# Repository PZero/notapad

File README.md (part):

<div align="center">

# notªpad

**An open wearable voice recorder with an open data layer. It records all day and keeps your recordings on devices you own; open, documented interfaces (files, JSON and an MCP server) let you choose which tools use them. A resin monolith you wear around your neck.**

### [▶ Live animated presentation](https://pzero.github.io/notapad/)

**Follow the build:** [Instagram](https://www.instagram.com/notapadlabs/) · [YouTube](https://www.youtube.com/@notapadlabs) · [TikTok](https://www.tiktok.com/@notapadlabs) · **Support it:** [Ko-fi](https://ko-fi.com/notapad)

</div>

## Contents
- [Overview](#overview)
- [The object](#the-object)
- [Architecture](#architecture)
- [How it works (planned)](#how-it-works-planned)
- [Electronics v0.1](#electronics-v01)
- [Pre-order verification](#pre-order-verification)
- [First firmware and app tests](#first-firmware-and-app-tests)
- [Test bench: exploration now, MCP server later](#test-bench-exploration-now-mcp-server-later)
- [Wallpapers](#wallpapers)
- [Manufacturing](#manufacturing)
- [Status and roadmap](#status-and-roadmap)
- [Support the project](#support-the-project)
- [Project history](#project-history)
- [Repository layout](#repository-layout)
- [Contributing](#contributing)
- [License](#license)
- [Authors](#authors)

## Overview
notªpad is a wearable recorder in the spirit of Plaud and Omi, but open. Two things set it apart: **continuous recording all day** and an **open MCP server**. It records all day, syncs over Bluetooth LE with a phone, and hands the audio to an **open MCP server**. The device itself only records: what happens next (playback, search, transcription, notes) is up to the tools the user picks, not a closed service.

Design goals:
- **Own your data.** Audio and notes stay with the user; every tool that reads them is replaceable.
- **No screen, no app to open.** Interaction is a squeeze gesture, three LEDs and a vibration motor.
- **Buildable by a small team.** Off-the-shelf parts (an Ebyte E73 nRF52840 module), a 4-layer board assembled by a PCBA service, a resin shell cast in a silicone mould.

> Honest status: this is a design in progress. Nothing has been manufactured yet; the first firmware and app tests (on a development board) have run on a development board (connection, recording, download and transcription work; deeper tests are pending). Figures such as runtime and capacity are estimates.

## The object
| | |
|---|---|
| Size | about 41 × 17.5 × 9 mm (it was 8 mm until 22 Nov; 38 mm is the board length), cast resin |
| Attachment | steel ring cast in with a bushing, so it cannot come off |
| Controls | touch sensors on **both** sides (metal strips as electrodes); a touch counts only when both are active (the "squeeze" gesture), to avoid accidental triggers from the chest |
| Signalling | 3 RGB LEDs behind a 10 mm front slit, vibration motor |
| Audio | 2 PDM microphones: one on the front face, one on the top face next to the ring (via a small channel) |
| Contacts | 4 exposed gold contacts on the back: 5V, GND (charging), SWDIO, SWCLK (firmware over cable in v0.1, later also OTA over BLE). They are also a deliberate aesthetic feature. Pogo pins live in the dock, not on the monolith |

| Back | Side | Finish options |
|---|---|---|
|  |  |  |

## Architecture
```mermaid
flowchart LR
  MIC[2 PDM microphones] --> NRF[nRF52840<br/>LC3 2x24 kbit/s]
  TOUCH[Touch sensors A+B] --> NRF
  NRF --> NAND[(256 MB NAND)]
  NRF --> OUT[3 RGB LEDs + vibration]
  NRF <-->|BLE| APP[Phone app]
  APP --> MCP[Open MCP server]
  MCP --> AI[Tools of the user's choice<br/>players, notes, transcription]
```
The real app and the MCP server are not started yet; a test app for a development board exists (see the roadmap).

### How it works (planned)
Next / planned, defined on 25 Nov 2026 and not built yet. It is a loop, and day to day you only use the app. The animated version is on the [presentation page](https://pzero.github.io/notapad/#how).
```mermaid
flowchart LR
  DEV[notªpad] -->|Bluetooth LE| APP[App<br/>desktop and mobile, same data]
  APP --> SRV[notªpad server<br/>backend + MCP server]
  SRV --> AI[Your tools<br/>for example an AI assistant]
  AI --> ART[Artifact<br/>interactive page]
  ART --> APP
```
1. The notªpad syncs its audio to the app; the app sends transcripts to the notªpad server.
2. The server is only a go-between (backend plus an open MCP server). Raw transcripts go to the user's own AI and are then deleted from the server; the data stays the user's. The server could also be self-hosted.
3. The AI of the user's choice runs a preset agent template: it splits the day into segments, summarises, links and shows.
4. The result is an interactive artifact, shown back in the app.

**Voice commands and integrations.** Working today in the test app: a spoken "Command, turn on the kitchen light" turns on a light (the test app calls Home Assistant directly). Next / planned: through MCP, the user's AI could act on other tools (calendar, tasks, notes, files, any MCP server).

## Electronics v0.1
- **Module:** Ebyte E73-2G4M08S1C (nRF52840), wire antenna at the board edge with keep-out.
- **Storage:** W25N02KV QSPI NAND, 256 MB (about 10 to 11 h of stereo LC3 audio).
- **Microphones:** the front one is an MSM261DGT006 (top-port PDM). On 25 Nov it replaced the MSM261DGT003 with the updated version indicated by its manufacturer; footprint and pinout still to be confirmed against the datasheet. Since 24 Nov the top one is a Vesper VM3011, a PDM microphone with acoustic wake-up: it listens with the clock stopped at about 10 uA (datasheet figure, preliminary) and wakes the processor when sound passes a self-adapting threshold. Stereo on a single data line.
- **Motion and sound emitter (24 Nov):** a 3-axis accelerometer (LIS2DH12, I2C) and a 4 x 4 mm magnetic buzzer on the back, driven by the second half of a dual MOSFET shared with the vibration motor. The joint Apple/Google specification against unwanted tracking (DULT) asks for a sound emitter (at least 60 phon at 25 cm) and recommends a motion sensor. **This is hardware preparation only, not compatibility:** Google requires registration and certification, and Apple requires its MFi programme, whose specifications are not public.
- **Power:** ~110 mAh LiPo (381620 candidate) with protection circuit, MCP73832 charger at 50 mA, 3.3 V LDO, and a P-MOSFET latch that disconnects everything when the battery reaches 3.50 V (idle draw below ~5 uA). The 5V contact re-arms the latch, goes directly to the nRF52840 VBUS pin (internal detection; the charger status read was dropped to free pins) and resets the MCU ("reset by putting it on charge"). A watchdog is always on.
- **Board:** 16.5 x 38 mm, 4 layers, 1.0 mm, ENIG or lead-free HASL (to be fixed at order), components on the top side only. Stackup: F.Cu signals, In1 continuous GND, In2 signals and power, B.Cu signals and GND; antenna keep-out on all layers. Zones: A (0-7 mm: pins, top microphone, charger, latch), B (7-20 mm: LEDs, touch ICs, LDO, passives), C (20-38 mm: E73 module and antenna). The motor and battery sit under the board.
- **Battery:** the 502025, 602030, 401020, 401230 and 402020 cells were ruled out (too wide, too long or too small). The candidate is the 381620 (3.8 x 16 x 20 mm, about 110 mAh, estimate from listings), with protection still to be confirmed; the 501520 does not fit the 9 mm monolith.
- **Estimated consumption:** about 4.6 mA average while recording, so about 20 h on the 110 mAh cell (estimate from datasheets, little margin without the DC-DC converter; to be measured). Memory, not battery, sets the limit for continuous recording: about 11 to 12 h of stereo audio in 256 MB, stretched by recording only when there is sound and by syncing during the day.

### What changed during design review (21 Nov 2026)
- **Pinout redone.** The E73 does not expose P0.11, P0.14, P0.16, P0.19, P0.21, P0.23, P0.25, P0.27 and P1.01, which the first pinout used. The new assignment is in [`docs/pinout_v0.1.md`](docs/pinout_v0.1.md); the 32 kHz crystal is dropped (firmware uses the internal LFRC).
- **Microphones replaced.** The first choice (LMD3526B261) is bottom-port; the MSM261DGT003 is top-port and in stock (replaced on 25 Nov by the updated MSM261DGT006, see the update below).
- **Space savings.** One resistor per LED on the common anode instead of one per colour (LEDs multiplexed, one colour at a time); an extra 1 uF capacitor on the latch so a reset at low battery does not power the device off.
- **Board closed on 4 layers.** With 2 layers 7 connections stayed open; the economy assembly tier does not accept 4 layers at 0.8 mm, so the board is 1.0 mm. Length fixed at 38 mm (at 35 mm 4 connections stayed open). Checks: ERC 0, DRC 0 violations, 0 unconnected, schematic-board parity 0.
- **Charger changed to MCP73831** (50 mA), chosen at the time to keep the number of extra-fee components down. *Superseded on 22 Nov by the MCP73832, see the pre-order verification below.*
- **Manufacturing route first fixed (late 21 Nov).** The XIAO carrier variant costs more than the E73 module, is 17.5 mm wide (as wide as the monolith) and has 13 GPIOs against about 20 needed; home assembly dropped (no hot plate or paste), so a PCBA service assembles every board. No distributor beats the one we use for the key chips, and a Basic-parts-only board is impossible (no BLE, NAND, PDM microphones, RGB LEDs or touch ICs in that library); 7 extra-fee parts stay. Q2 stays a dual 2N7002DW; NAND and charger stay extra-fee parts.
- **Parts review.** E73 variant with only an external-antenna socket rejected; the 256 MB NAND confirmed after comparing alternatives; microphones rotated by 180 degrees in the placement file (checked in the assembler's preview). An alternative manufacturing variant was prepared and dropped for v0 (no microphone stock, higher quote).
- **Charger stays on the monolith** (not in the dock): unpowered contacts outside the dock, CHRG signal available, full 4.2 V charge.

### Update, 25 Nov 2026
- **Software architecture defined** (server, MCP server, preset agent template, desktop and mobile app): see [How it works (planned)](#how-it-works-planned). A plan, not built.
- **Front microphone:** MK1 changes from the MSM261DGT003 to the MSM261DGT006, the updated version indicated by its manufacturer, who confirmed the same footprint, pinout and sound hole (the board does not change) and recommends a 0.8 to 1.0 mm hole in the resin plus a gasket. The bill of materials and KiCad files are not updated to the DGT006 yet.
- **Project identity:** public contact notapad.team@gmail.com, the name @notapadlabs on Instagram, YouTube and TikTok, NªP monogram as logo. First post ("Meet notªpad") published; posts 3 to 7 scheduled until 5 Dec (4 to 5 a week at launch, then 2). Nordic Semiconductor registered the project with its technical support.
- **One fundraising goal:** 3 to 5 prototypes (about €300), individuals and companies adding up; see [Support the project](#support-the-project).
- **Board still unfrozen.** The v0.1 board of 24 Nov stays unfrozen. The VM3011 microphone may no longer be obtainable, so an alternative wake-on-sound microphone will be evaluated.
- **Subtitle:** "an open wearable voice recorder with an open data layer": the device records, the AI is one of the tools you choose.
- **Samples and contests:** sample and development-kit requests sent to the makers of the main components (nothing received yet); the project will enter two hardware design contests (deadlines 24 and 31 Jan 2027). A European grant was considered and dropped because its rules exclude AI-assisted development.
- **Support:** donations are open on [Ko-fi](https://ko-fi.com/notapad) and through the repository's Sponsor button; GitHub Sponsors is awaiting approval.
- **Sponsor search ongoing; nothing agreed,** and no production exclusivity for now.

### Update, 24 Nov 2026
- **Board regenerated, not frozen:** same 16.5 x 38 mm, 4 layers; now with the wake-on-sound microphone, the accelerometer and the buzzer described above (ERC 0, DRC 0, parity 0, 130 vias). Still under review: buzzer volume and sound outlet, the acoustic channel of the VM3011 through the shells, and VM3011 availability (out of stock at one distributor, preliminary datasheet). The final Gerber, bill of materials and placement files come after the review.
- **Pins freed without losing functions:** 5V straight to VBUS, charger status read removed, I2C on two freed pins. Three RGB LEDs and gestures unchanged.
- **Verification rerun on the new board:** 71 tests, 45 passed, 23 known warnings, 2 not verifiable, 1 to reconfirm (a component page to read again). It found and got fixed two real errors (placement rotation of the new microphone, a footprint without courtyard); a wrong charger code in the bill of materials for the manufacturers was corrected.
- **Sponsorship:** sponsor search ongoing; nothing agreed. The manufacturer is not decided.
- **Figures corrected:** about 20 h on the 110 mAh cell (estimate); the 256 MB memory holds 11 to 12 h of continuous stereo.
- **Test bench:** firmware 0.2.0 (records only on sound) and app 0.10.0 (full-precision Whisper on the device) published; next are the Android app and the architecture of the open MCP server.
- **Non-commercial for now;** licences confirmed.

### Update, 22 Nov 2026
- **Test bench defined (evening), now one animated scene on the presentation page ([#bench](https://pzero.github.io/notapad/#bench)):** Whisper with word timing and speech detection, speaker recognition (WeSpeaker), tap gestures and first voice-command tests; see [Test bench](#test-bench-exploration-now-mcp-server-later). Exploration only; the features are meant to move into the MCP server later.
- **Licences chosen:** CERN-OHL-S-2.0 for hardware, MIT for software and documents.
- **Presentation animation fixed:** the flicker while the monolith rotates came from the internal battery model sharing a face with the shell (now 15 x 19 x 3.2 mm, 0.2 mm inside). Page layout reworked for phones; group, gesture and MCP scenes redone. Checked at 375, 390 and 1280 px, not on a real iPhone. The monolith length is 41 mm; 38 mm is the board length.
- **Wallpapers approved:** all eight phone wallpapers, published below; the three LEDs are drawn as separate lights.
- **Firmware and app tested on a development board** (see below): connection, recording and download confirmed on a real XIAO nRF52840 Sense; automatic Whisper transcription added to the app; the app stays a PWA also for Android (https page still to publish). Battery 501520 dropped (does not fit 9 mm).
- **Sponsor search started** (see below). Batteries 602030, 401020, 401230 and 402020 ruled out; 381620 is the candidate (estimates).
- **Contacts:** flat-head target contacts (monolith) and single pogo pins (charging base) identified; wiring plan for the base (8 solder joints).
- **Pre-order verification, third run:** 41 passed, 25 warnings, 1 failure, 2 not verifiable (69 tests). Charger changed to the MCP73832; monolith now **9 mm** (at 8 mm only 0.1 mm of resin was left per face, now 0.6 mm); contact targets 2.0 x 4.0 mm with the tip 0.1 mm out of the back, and the four holes widened from 1.0 to 1.1 mm (only the drill files changed, copper identical, DRC clean). The section drawing of the target in the 9 mm monolith is [`verifica/target_sezione.png`](verifica/target_sezione.png) (labels in Italian).

Documents: pinout in [`docs/pinout_v0.1.md`](docs/pinout_v0.1.md); bill of materials and netlist in [`jlc/`](jlc/); KiCad project and generators in [`kicad/`](kicad/).

## Pre-order verification
The board is generated by scripts, which makes mistakes repeatable too. On 22 Nov 2026, before paying for assembly, a reviewer agent went through the whole board with **69 automated tests in 8 areas**:

| Area | What is checked |
|---|---|
| A | Rules, ERC and DRC, also with the ignored rules switched back on |
| B | Pinout of every component against its datasheet |
| C | Schematic symbol against footprint |
| D | Circuit analysis with numbers: latch, reset, dividers, LEDs, LDO, microphones, consumption |
| E | Bill of materials and placement file for the assembler: codes, extra-fee parts, rotations |
| F | Mechanics: courtyards, stack-up in the thickness, battery, motor, LEDs in the slit, microphone ports, contacts, antenna keep-out |
| G | Gerber files |
| H | Consistency between documents |

Every value is cross-checked against at least two independent sources (datasheet, the single Python definition, schematic, netlist, board, Gerber, BOM and placement file, documents). Each test is a repeatable script in [`verifica/`](verifica/) that ends in PASS, WARN, FAIL or NOT VERIFIABLE, so the review can be rerun before every order.

**First run:** 37 passed, 26 warnings, 3 failures, 2 not verifiable. **Second run, after the charger fix:** 39 / 26 / 2 / 2. **Third run, after the 9 mm and 1.1 mm hole changes:** 41 passed, 25 warnings, 1 failure, 2 not verifiable. The real problems it found:
- **Charger.** The MCP73831 status output is tri-state and powered from the 5V rail, so it would have pulled an nRF52840 pin to about 5 V, above its maximum. Fixed by switching to the MCP73832: same footprint and pinout, open-drain output, Gerber files unchanged.
- **Assembly tier (open, the one failure left).** the assembly service lists the E73 module as standard-tier assembly only, so the 97 EUR economy-tier quote has to be rechecked before paying.
- **Thickness (fixed).** With the 3 mm module and the 3.8 mm battery, 8 mm left 0.1 mm of resin per face; at 9 mm there is 0.6 mm. Only the shells change.
- **Contact holes (fixed).** The 2.0 x 4.0 mm target contacts need 1.1 mm holes instead of 1.0 mm; only the drill files changed.

**Fourth run (24 Nov), on the regenerated board:** 71 tests, 45 passed, 23 known warnings, 2 not verifiable, 1 to reconfirm. It found two real errors, both fixed: the placement rotation of the new microphone and a footprint without courtyard.

What came out clean: ERC and DRC at 0, schematic-board parity 0, empty antenna keep-out. The remaining warnings concern shells, firmware and bring-up, not the board. A review like this cannot replace testing the real boards, and it does not guarantee they will work.

## First firmware and app tests
Started on 22 Nov 2026, before the v0.1 boards arrive. They run on a **Seeed XIAO nRF52840 Sense** with a battery: a development board with the same nRF52840 chip, a PDM microphone and 2 MB of flash, used to try the whole chain early.
- **Firmware** ([`firmware/xiao-prova/`](firmware/xiao-prova/), Arduino with the Bluefruit library): records at 16 kHz, compresses with IMA ADPCM and stores the audio in a ring of 512 sectors of 4 KB, about 4 minutes. At 80% full it asks to sync and the connected app downloads by itself. Each sector is erased only after the app has received it, verified its CRC and saved it. Shutdown at 3.50 V and a watchdog are included.
- **App** ([`app/`](app/)): a web app (PWA), local-only for now (localhost, Web Bluetooth in Edge or Chrome). It stores in the browser (IndexedDB), with playback and WAV export, and no cloud. Since 22 Nov it also **transcribes automatically after each sync** with Whisper running in the browser (transformers.js in a Web Worker, WebGPU or WASM; small model on a PC, base on a phone; Italian), keeping the time of each sentence, with TXT export. The audio never leaves the device. Test: 17 s of Italian speech in 4.8 s with whisper-base on WebGPU.
- **Honest status:** the firmware was flashed on a real XIAO nRF52840 Sense and tested with the app on 22 Nov: Bluetooth connection, recording and audio download work. **Not tested in depth yet:** automatic sync at 80%, audio quality, download speed, the small Whisper model, Edge as an installed app and an Android phone. The final firmware for the v0.1 board (Zephyr is the option) is separate and still on hold; the phone app stays a PWA for now (Flutter postponed).

## Test bench: exploration now, MCP server later
This is an **exploration phase, not the product**. The XIAO nRF52840 Sense firmware plus the local app (Web Bluetooth, data kept only in the browser) are a test bench to learn which software features work and how well, before the real board exists. Most of it was added on 22 Nov 2026 and improved on 23 Nov; speed and error rates are not measured yet.
- **Whisper in the browser** (transformers.js, models that return the time of every word): the audio never leaves the device. **Updated 23 Nov (app 0.10.0):** the decoder had been running compressed to 4 bits on WebGPU, the main cause of errors in Italian; it now runs at full precision, and on a PC with WebGPU the automatic model is large-v3-turbo (a download of about 1.6 GB, once). Audio goes to the model in windows of 10 to 25 s cut at pauses, with levelled volume and a filter for invented or repeated phrases. Transcription starts on request (automatically only for quick commands); models can be loaded from a local folder to work offline. Quality is better by observation, not measured.
- **Who is speaking:** voice prints with WeSpeaker ResNet34. The transcript shows "Me" (the owner, whose profile comes from the microphone or from confirming "that's me" on a transcript) and "Speaker 1, 2, 3...". Text is always in chronological order.
- **Gestures** on the device (motion sensor): double tap starts or stops recording; single tap is a command (5 yellow flashes, the next 6 seconds become a separate piece downloaded with priority, then recording continues).
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
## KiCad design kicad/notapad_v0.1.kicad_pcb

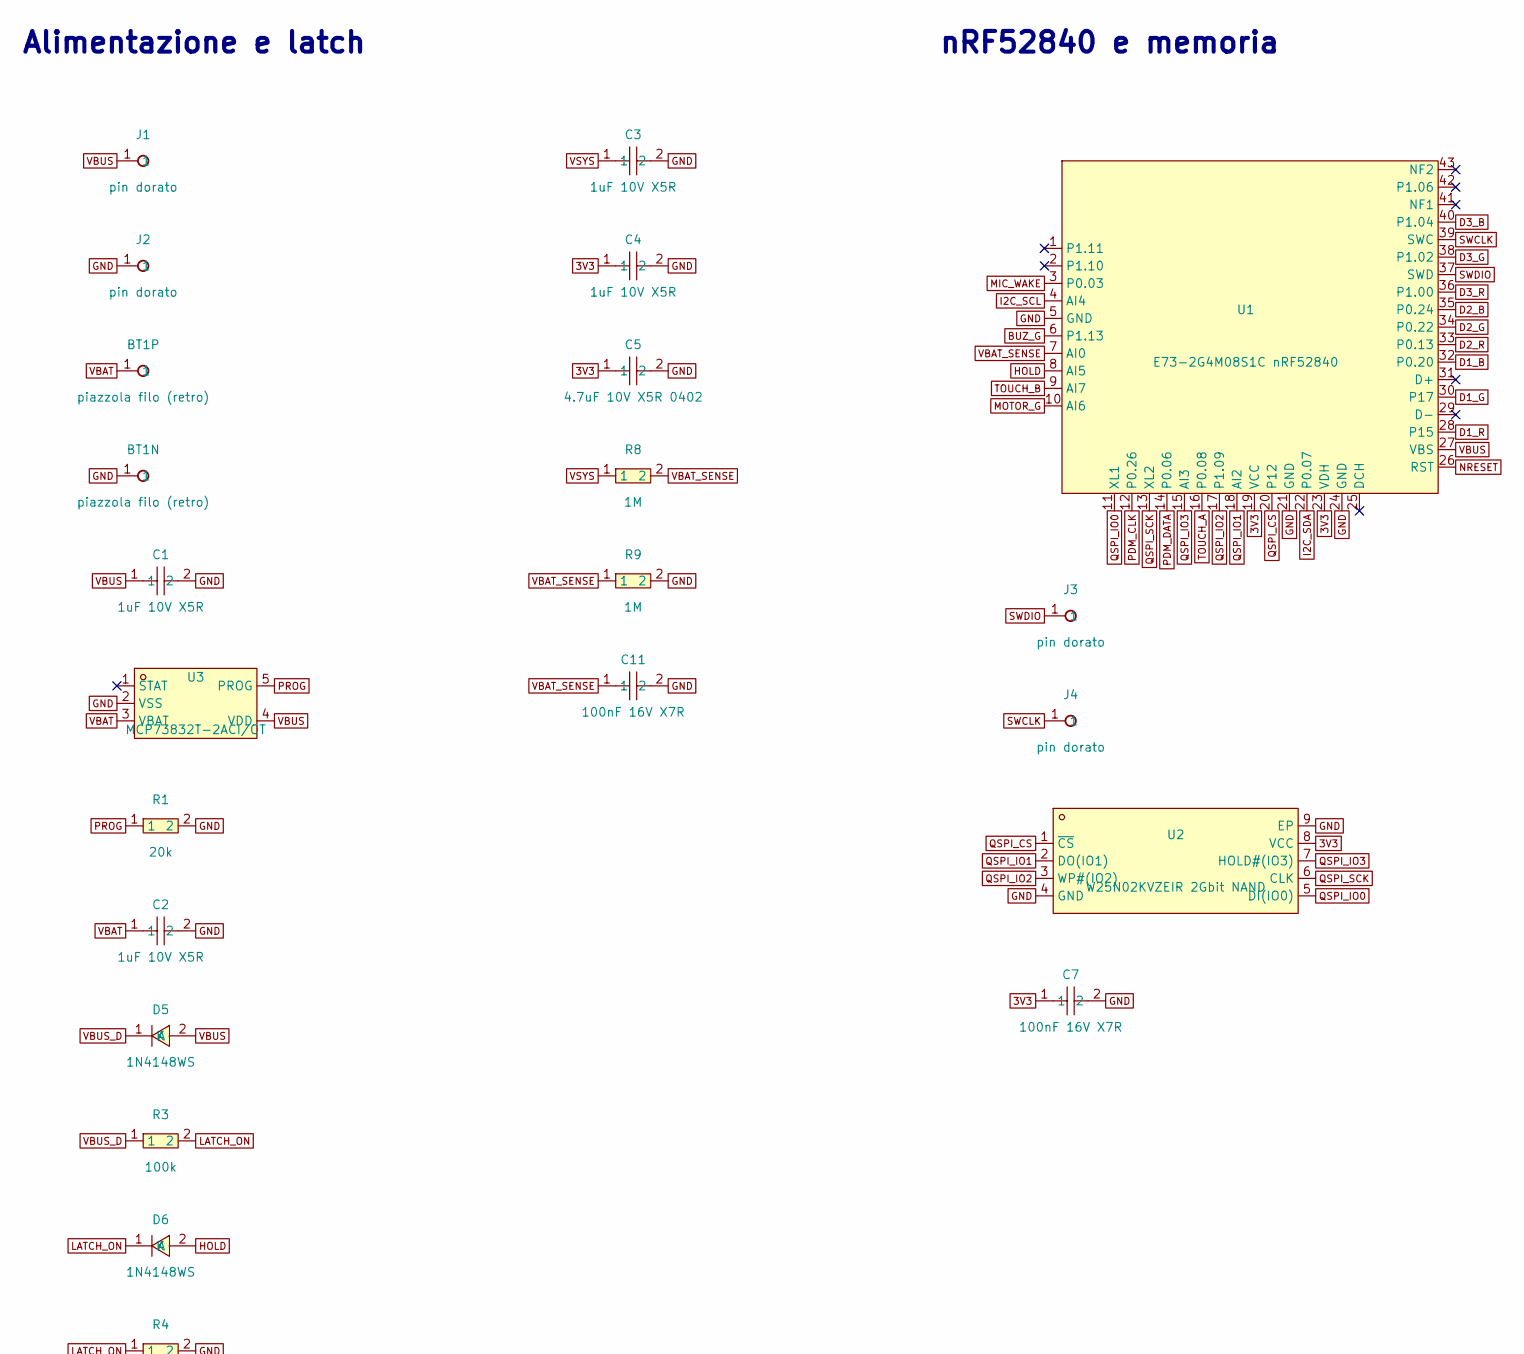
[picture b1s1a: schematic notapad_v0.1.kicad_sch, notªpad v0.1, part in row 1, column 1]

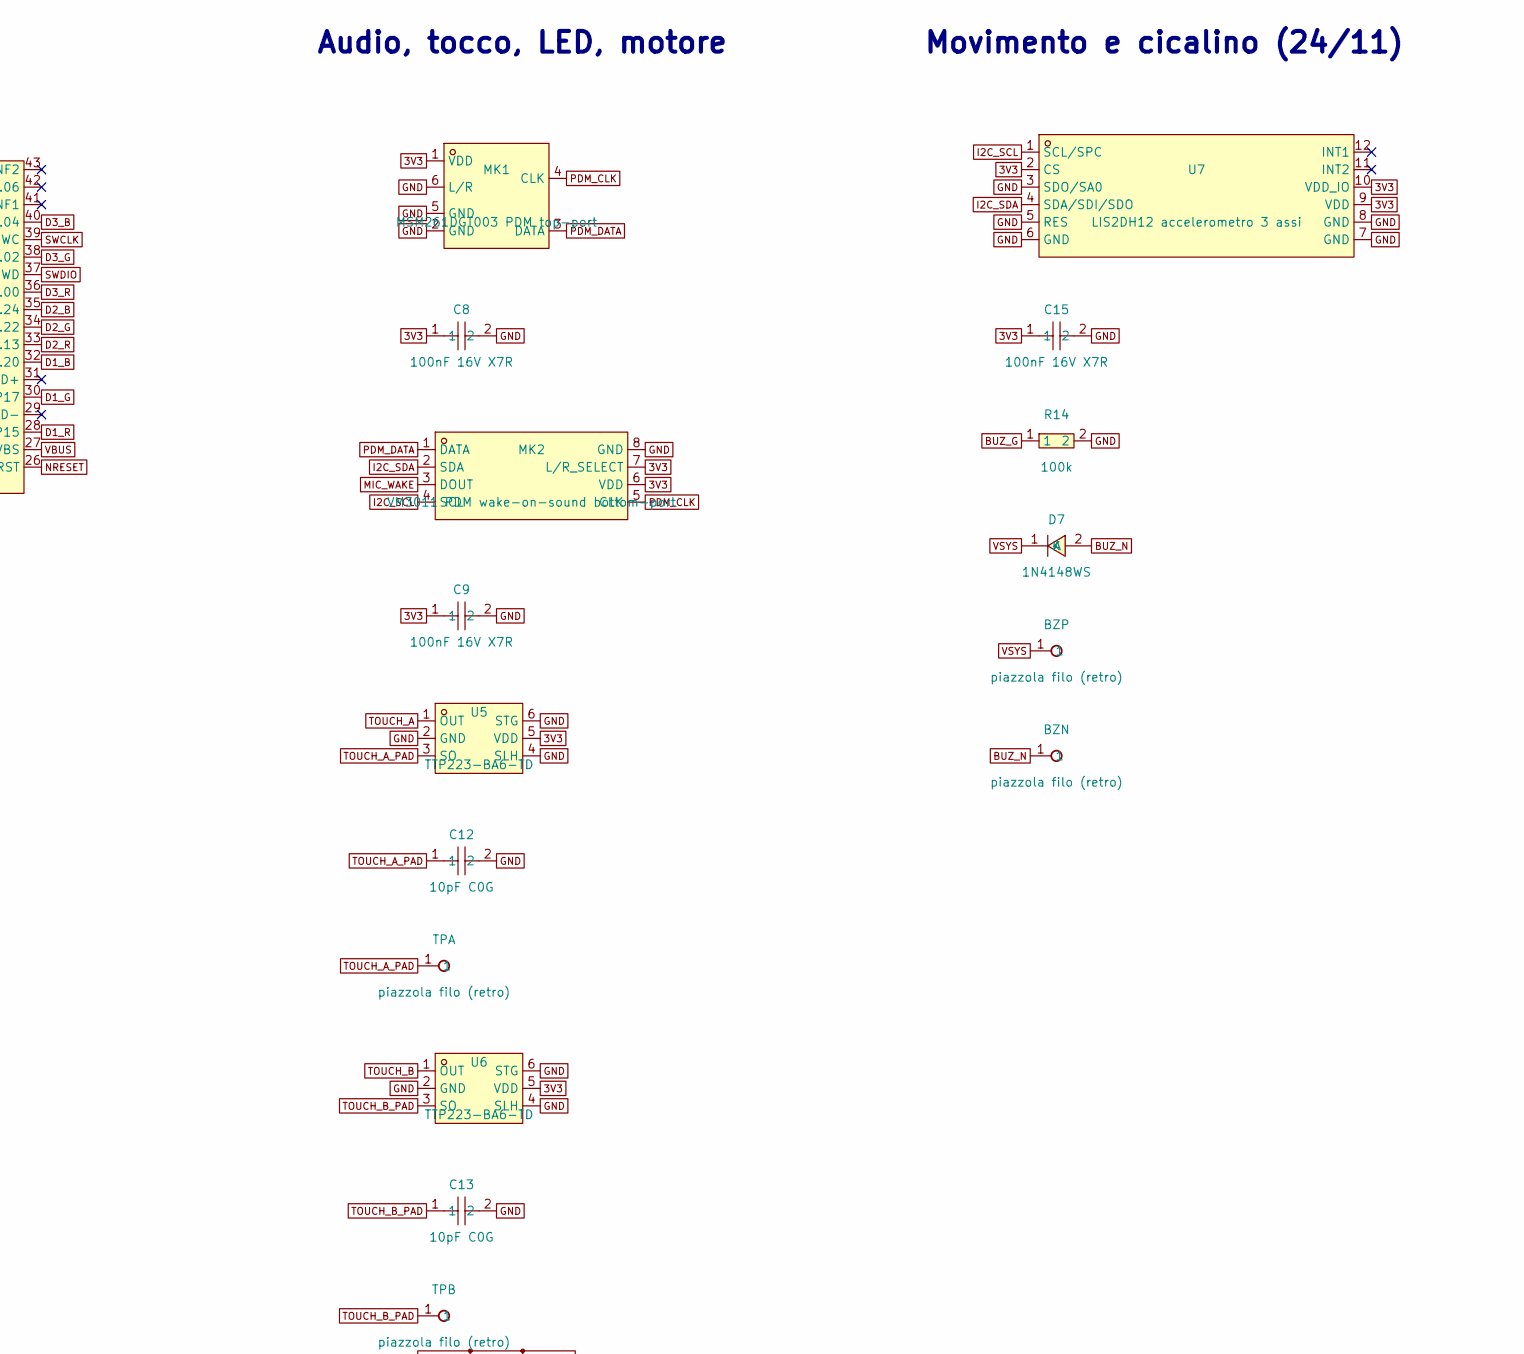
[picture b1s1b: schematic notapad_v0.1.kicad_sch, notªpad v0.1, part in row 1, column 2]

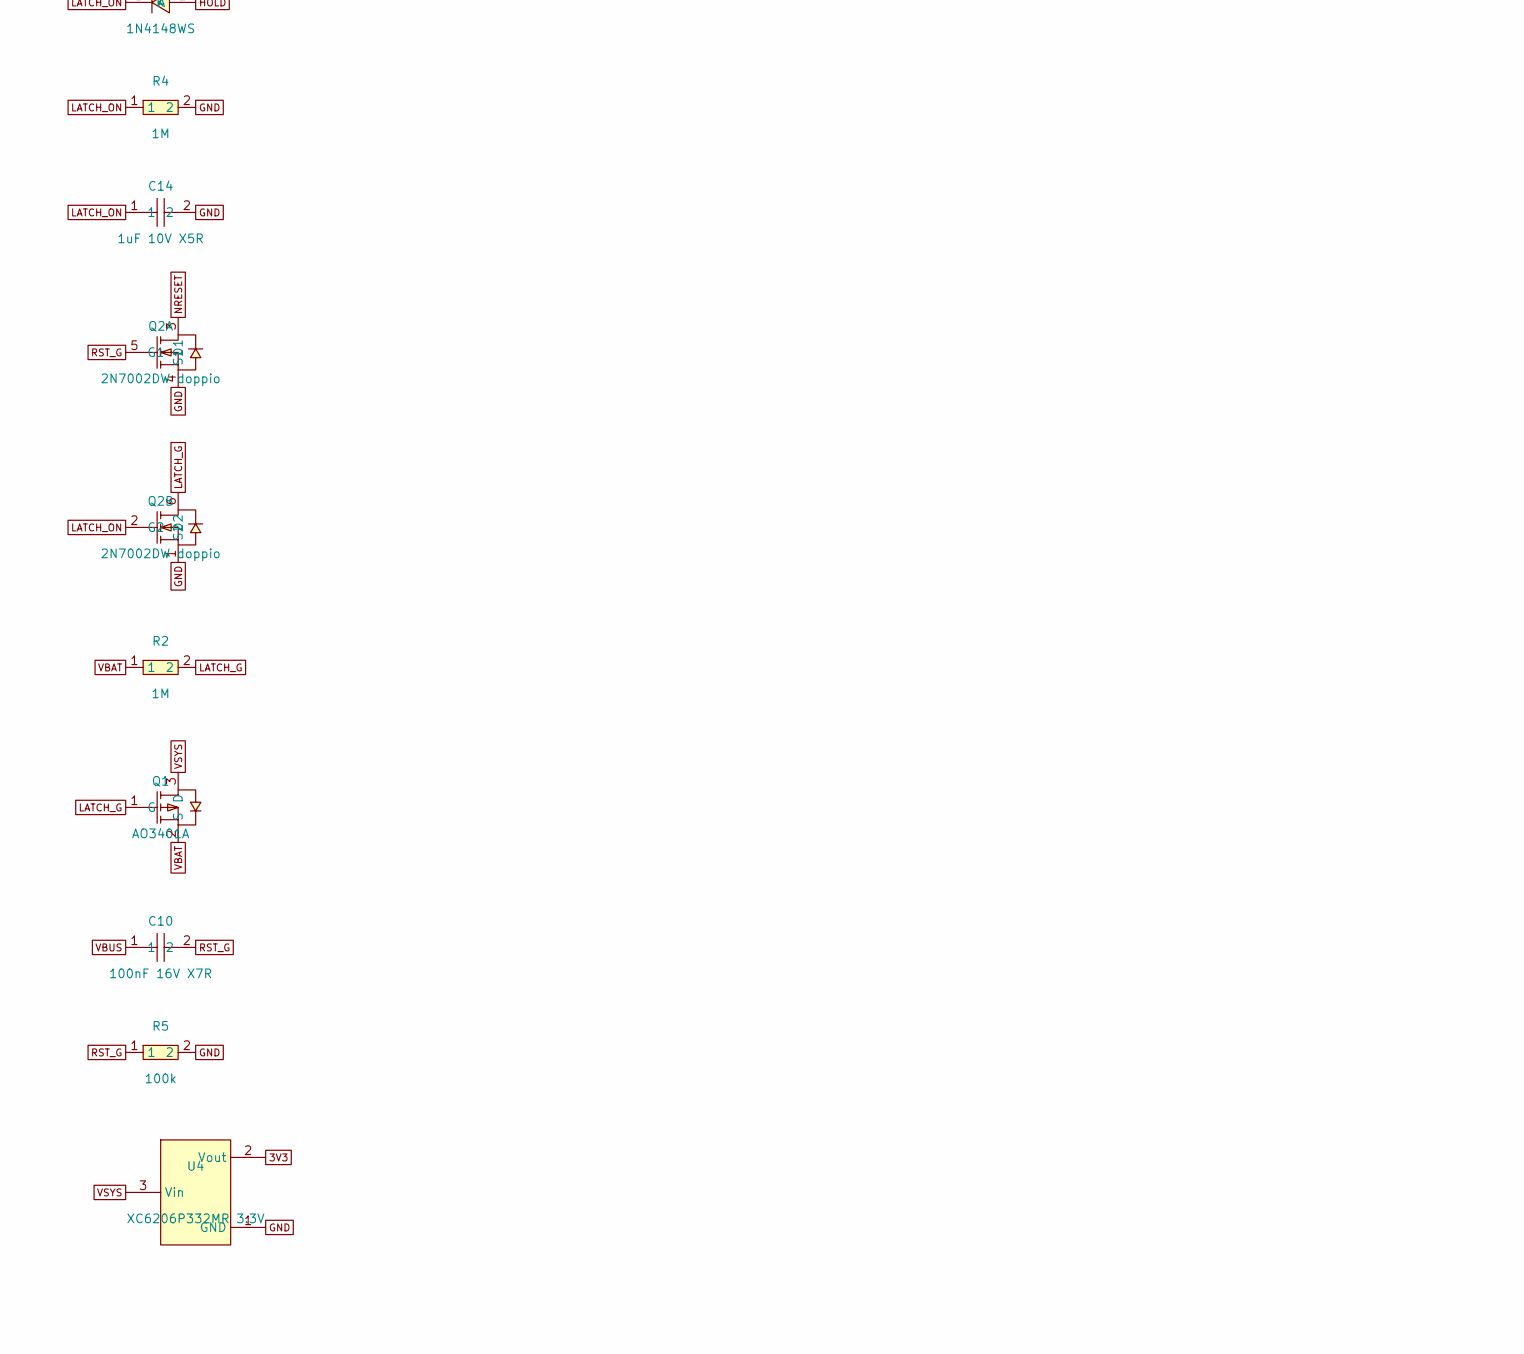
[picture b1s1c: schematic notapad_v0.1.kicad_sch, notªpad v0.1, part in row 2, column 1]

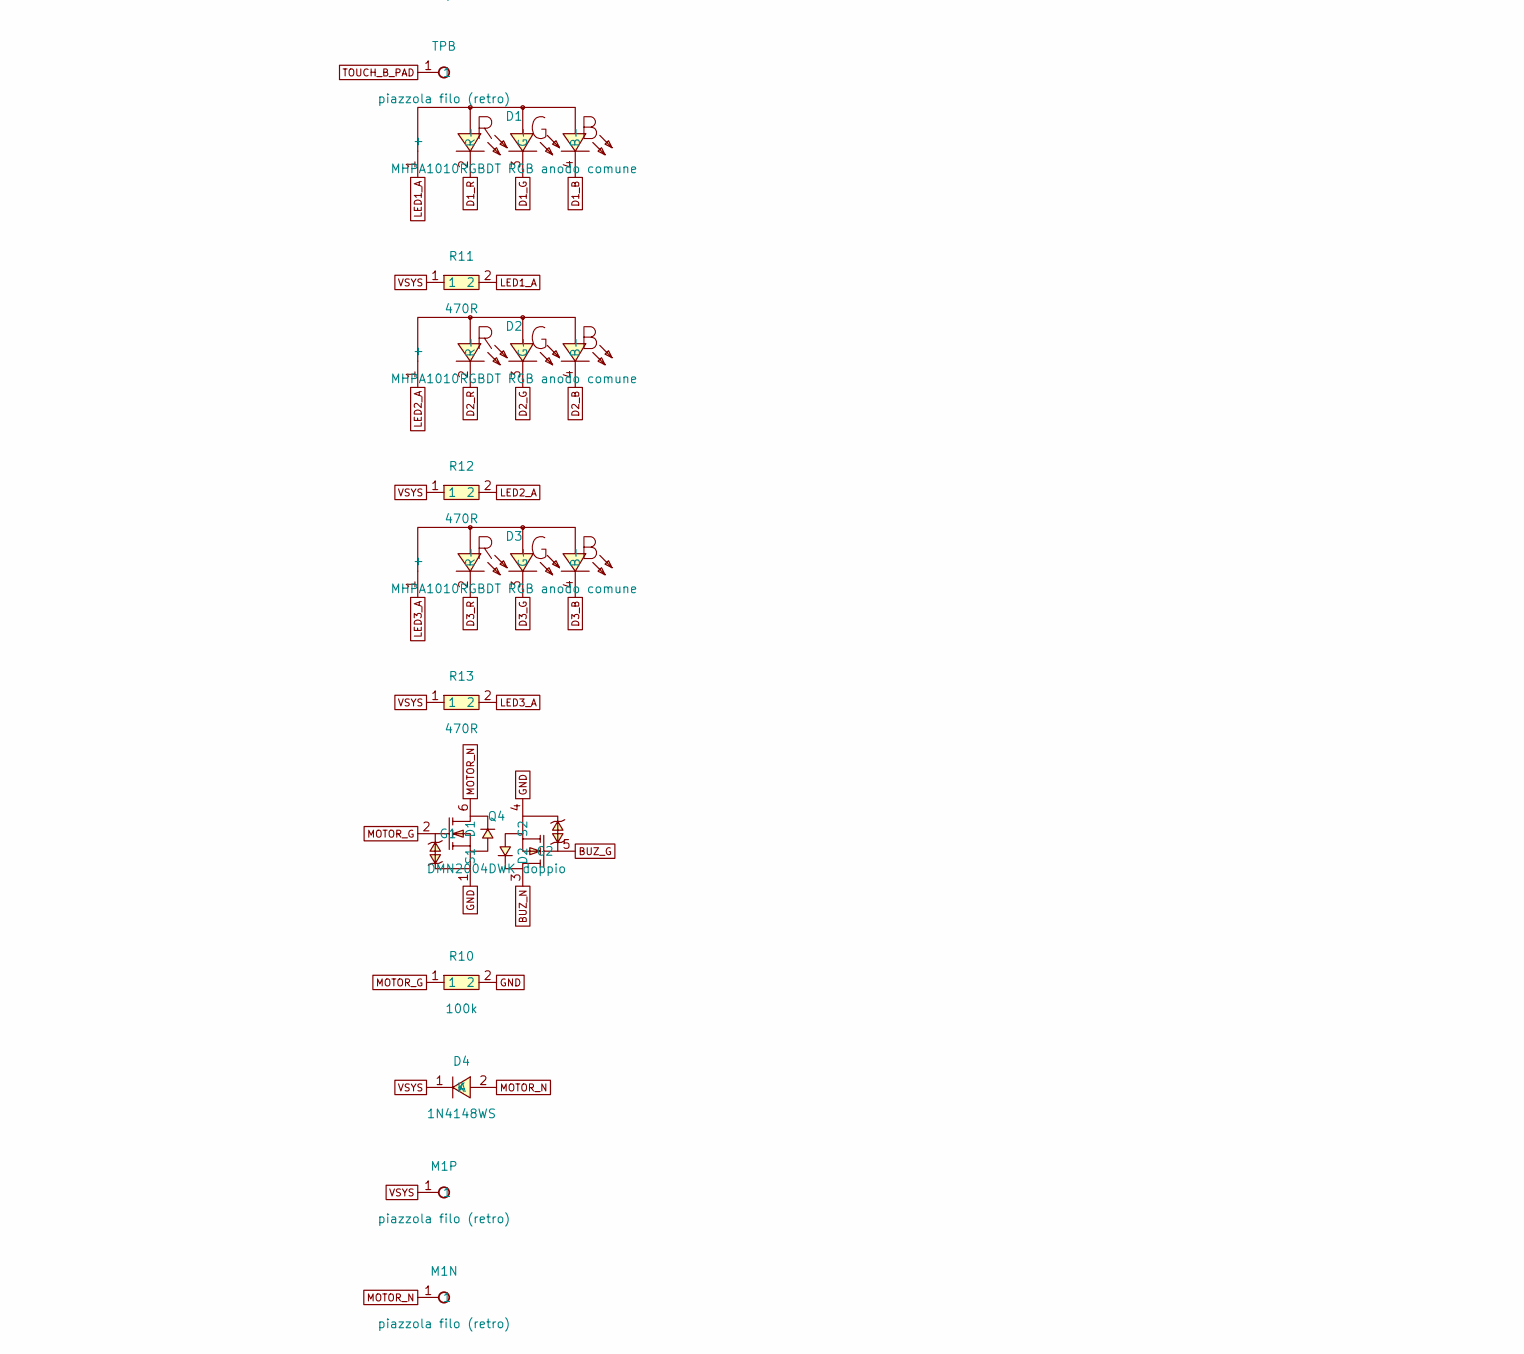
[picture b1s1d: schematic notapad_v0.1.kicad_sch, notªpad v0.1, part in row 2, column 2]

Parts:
BT1N, BT1P: piazzola filo (retro); PAD_BOT_1.2x1.6
BZN: piazzola filo (retro); PAD_BOT_1.2x1.6
BZP: piazzola filo (retro); PAD_BOT_1.2x1.6
C1, C2, C3, C4, C14: 1uF 10V X5R; C0402; LCSC Part C52923
C5: 4.7uF 10V X5R 0402; C0402; LCSC Part C23733
C7, C8, C9, C10, C11, C15: 100nF 16V X7R; C0402; LCSC Part C1525
C12, C13: 10pF C0G; C0402; LCSC Part C32949
D1, D2, D3: MHPA1010RGBDT RGB anodo comune; LED-ARRAY-SMD_4P-L1.0-W1.0-TR-RD; LCSC Part C404280
D4, D5, D6, D7: 1N4148WS; SOD-323_L1.8-W1.3-LS2.5-RD; LCSC Part C2128
J1, J2, J3, J4: pin dorato; PIN_THT_1.6
M1N, M1P: piazzola filo (retro); PAD_BOT_1.2x1.6
MK1: MSM261DGT003 PDM top-port; MIC-SMD_6P-L4.0-W2.0_LMD4020T261-OC3; LCSC Part C48227730
MK2: VM3011 PDM wake-on-sound bottom-port; SENSOR-SMD_VM3011-U1; LCSC Part C7149370
Q1: AO3401A; SOT-23_L2.9-W1.3-P1.90-LS2.4-BR; LCSC Part C15127
Q2: 2N7002DW doppio; SOT-363_L2.0-W1.3-P0.65-LS2.1-TL; LCSC Part C83571
Q4: DMN2004DWK doppio; SOT-363_L2.0-W1.3-P0.65-LS2.1-TL; LCSC Part C156343
R1: 20k; R0402; LCSC Part C25765
R2, R4, R8, R9: 1M; R0402; LCSC Part C26083
R3, R5, R10, R14: 100k; R0402; LCSC Part C25741
R11, R12, R13: 470R; R0402; LCSC Part C25117
TPA: piazzola filo (retro); PAD_BOT_1.2x1.6
TPB: piazzola filo (retro); PAD_BOT_1.2x1.6
U1: E73-2G4M08S1C nRF52840; WIRELM-SMD_E73-2G4M08S1C; LCSC Part C356849
U2: W25N02KVZEIR 2Gbit NAND; WSON-8_L8.0-W6.0-P1.27-TL-EP-1; LCSC Part C3010298
U3: MCP73832T-2ACI/OT; SOT-23-5_L3.0-W1.7-P0.95-LS2.8-BL; LCSC Part C38066
U4: XC6206P332MR 3.3V; SOT-23-3_L2.9-W1.6-P1.90-LS2.8-BR; LCSC Part C5446
U5, U6: TTP223-BA6-TD; SOT-23-6_L2.9-W1.6-P0.95-LS2.9-BL; LCSC Part C42422127
U7: LIS2DH12 accelerometro 3 assi; LGA-12_L2.0-W2.0-P0.50-BL; LCSC Part C110926

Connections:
3V3: C4.1, C5.1, C7.1, C8.1, C9.1, C15.1, MK1.1 (VDD), MK2.6 (VDD), MK2.7 (L/R_SELECT), U1.19 (VCC), U1.23 (VDH), U2.8 (VCC), U4.2 (Vout), U5.5 (VDD), U6.5 (VDD), U7.2 (CS), U7.9 (VDD), U7.10 (VDD_IO)
BUZ_G: Q4.5 (G2), R14.1, U1.6 (P1.13)
BUZ_N: BZN.1, D7.2 (A), Q4.3 (D2)
D1_B: D1.4 (B-), U1.32 (P0.20)
D1_G: D1.3 (G-), U1.30 (P17)
D1_R: D1.2 (R-), U1.28 (P15)
D2_B: D2.4 (B-), U1.35 (P0.24)
D2_G: D2.3 (G-), U1.34 (P0.22)
D2_R: D2.2 (R-), U1.33 (P0.13)
D3_B: D3.4 (B-), U1.40 (P1.04)
D3_G: D3.3 (G-), U1.38 (P1.02)
D3_R: D3.2 (R-), U1.36 (P1.00)
GND: BT1N.1, C1.2, C2.2, C3.2, C4.2, C5.2, C7.2, C8.2, C9.2, C11.2, C12.2, C13.2, C14.2, C15.2, J2.1, MK1.2 (GND), MK1.5 (GND), MK1.6 (L/R), MK2.8 (GND), Q2.1 (S2), Q2.4 (S1), Q4.1 (S1), Q4.4 (S2), R1.2, R4.2, R5.2, R9.2, R10.2, R14.2, U1.5 (GND), U1.21 (GND), U1.24 (GND), U2.4 (GND), U2.9 (EP), U3.2 (VSS), U4.1 (GND), U5.2 (GND), U5.4 (SLH), U5.6 (STG), U6.2 (GND), U6.4 (SLH), U6.6 (STG), U7.3 (SDO/SA0), U7.5 (RES), U7.6 (GND), U7.7 (GND), U7.8 (GND)
HOLD: D6.2 (A), U1.8 (AI5)
I2C_SCL: MK2.4 (SCL), U1.4 (AI4), U7.1 (SCL/SPC)
I2C_SDA: MK2.2 (SDA), U1.22 (P0.07), U7.4 (SDA/SDI/SDO)
LATCH_G: Q1.1 (G), Q2.6 (D2), R2.2
LATCH_ON: C14.1, D6.1 (K), Q2.2 (G2), R3.2, R4.1
LED1_A: D1.1 (+), R11.2
LED2_A: D2.1 (+), R12.2
LED3_A: D3.1 (+), R13.2
MIC_WAKE: MK2.3 (DOUT), U1.3 (P0.03)
MOTOR_G: Q4.2 (G1), R10.1, U1.10 (AI6)
MOTOR_N: D4.2 (A), M1N.1, Q4.6 (D1)
NRESET: Q2.3 (D1), U1.26 (RST)
PDM_CLK: MK1.4 (CLK), MK2.5 (CLK), U1.12 (P0.26)
PDM_DATA: MK1.3 (DATA), MK2.1 (DATA), U1.14 (P0.06)
PROG: R1.1, U3.5 (PROG)
QSPI_CS: U1.20 (P12), U2.1 (~CS)
QSPI_IO0: U1.11 (XL1), U2.5 (DI(IO0))
QSPI_IO1: U1.18 (AI2), U2.2 (DO(IO1))
QSPI_IO2: U1.17 (P1.09), U2.3 (WP#(IO2))
QSPI_IO3: U1.15 (AI3), U2.7 (HOLD#(IO3))
QSPI_SCK: U1.13 (XL2), U2.6 (CLK)
RST_G: C10.2, Q2.5 (G1), R5.1
SWCLK: J4.1, U1.39 (SWC)
SWDIO: J3.1, U1.37 (SWD)
TOUCH_A: U1.16 (P0.08), U5.1 (OUT)
TOUCH_A_PAD: C12.1, TPA.1, U5.3 (SO)
TOUCH_B: U1.9 (AI7), U6.1 (OUT)
TOUCH_B_PAD: C13.1, TPB.1, U6.3 (SO)
VBAT: BT1P.1, C2.1, Q1.2 (S), R2.1, U3.3 (VBAT)
VBAT_SENSE: C11.1, R8.2, R9.1, U1.7 (AI0)
VBUS: C1.1, C10.1, D5.2 (A), J1.1, U1.27 (VBS), U3.4 (VDD)
VBUS_D: D5.1 (K), R3.1
VSYS: BZP.1, C3.1, D4.1 (K), D7.1 (K), M1P.1, Q1.3 (D), R8.1, R11.1, R12.1, R13.1, U4.3 (Vin)

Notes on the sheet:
Alimentazione e latch
nRF52840 e memoria
Audio, tocco, LED, motore
Movimento e cicalino (24/11)

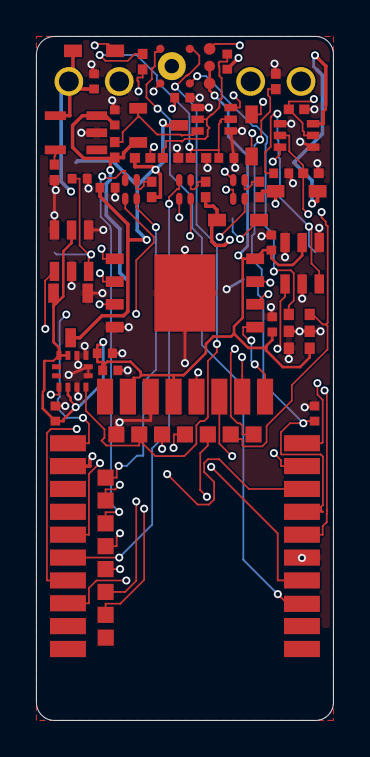
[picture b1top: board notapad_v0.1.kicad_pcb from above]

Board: 4 copper layers, 16.5 x 38.0 mm, 57 parts (0 on the bottom side), 46 nets.

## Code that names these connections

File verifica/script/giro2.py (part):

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

def B05():
    bad, p = _pinchk("U2", {"1": ("~{CS}", "QSPI_CS"), "2": ("DO(IO1)", "QSPI_IO1"), "3": ("WP#(IO2)", "QSPI_IO2"), "4": ("GND", "GND"), "5": ("DI(IO0)", "QSPI_IO0"),
                            "6": ("CLK", "QSPI_SCK"), "7": ("HOLD#(IO3)", "QSPI_IO3"), "8": ("VCC", "3V3"), "9": ("EP", "GND")})
    return ("PASS" if not bad else "FAIL"), ("1 /CS, 2 IO1, 3 IO2, 4 GND, 5 IO0, 6 CLK, 7 IO3, 8 3V3, EP GND: coincide" if not bad else f"differenze {bad}")


def B06():
    r = {}
    r["MK1"], _ = _pinchk("MK1", {"1": ("VDD", "3V3"), "2": ("GND", "GND"), "3": ("DATA", "PDM_DATA"), "4": ("CLK", "PDM_CLK"), "5": ("GND", "GND"), "6": ("L/R", "GND")})
    # 24/11: MK2 = VM3011 (datasheet U0.0.8: 1 DATA, 2 SDA, 3 DOUT, 4 SCL, 5 CLK, 6 VDD, 7 L/R, 8 GND; VDD 1,6-3,6 V)
    r["MK2"], _ = _pinchk("MK2", {"1": ("DATA", "PDM_DATA"), "2": ("SDA", "I2C_SDA"), "3": ("DOUT", "MIC_WAKE"), "4": ("SCL", "I2C_SCL"),
                                  "5": ("CLK", "PDM_CLK"), "6": ("VDD", "3V3"), "7": ("L/R_SELECT", "3V3"), "8": ("GND", "GND")})
    ok = not any(r.values())
    return ("PASS" if ok else "FAIL"), ("MK1 MSM261: 1 VDD, 2/5 GND, 3 DATA, 4 CLK, 6 L/R=GND, top-port; MK2 VM3011: 1 DATA, 2 SDA, 3 DOUT=MIC_WAKE, 4 SCL, 5 CLK, "
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

def B07():
    bad, p = _pinchk("U3", {"2": ("VSS", "GND"), "3": ("VBAT", "VBAT"), "4": ("VDD", "VBUS"), "5": ("PROG", "PROG")})
    d = D(); lcsc, v = d.P["CHG"][2], d.P["CHG"][3]
    r1 = d.P[d.C["R1"][0]][3]
    iprog = 1000 / 20 if r1 == "20k" else None
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    if lcsc == "C424093":
        return "FAIL", "U3 è ancora MCP73831 (STAT tri-state a 5 V su P0.07)"
    if lcsc == "C38066" and not stat and "1" not in d.C["U3"][1]:
        return "PASS", ("U3 MCP73832T-2ACI/OT (C38066), STAT non collegato dal 24/11 (P0.07 ora I2C_SDA): nessun percorso dal 5V a un GPIO; "
                        "lo stato di carica si ricava da VBUS e dalla tensione della batteria")
    return "FAIL", f"configurazione inattesa: {lcsc}, rete STAT {stat}"


def B09():
    bad, _ = _pinchk("U4", {"1": ("GND", "GND"), "2": ("Vout", "3V3"), "3": ("Vin", "VSYS")})
    return ("PASS" if not bad else "FAIL"), ("1 GND, 2 Vout=3V3, 3 Vin=VSYS (Torex MR: VSS/VOUT/VIN)" if not bad else f"{bad}")


def B10():
    b1, _ = _pinchk("Q1", {"1": ("G", "LATCH_G"), "2": ("S", "VBAT"), "3": ("D", "VSYS")})
    b4, _ = _pinchk("Q4", {"1": ("S1", "GND"), "2": ("G1", "MOTOR_G"), "6": ("D1", "MOTOR_N"), "4": ("S2", "GND"), "5": ("G2", "BUZ_G"), "3": ("D2", "BUZ_N")})
    ok = not b1 and not b4
    return ("PASS" if ok else "FAIL"), ("Q1 G=LATCH_G S=VBAT D=VSYS; Q4 DMN2004DWK: FET1 S=GND G=MOTOR_G D=MOTOR_N, FET2 S=GND G=BUZ_G D=BUZ_N "
                                        "(0,5 ohm a 2,5 V, 540 mA); soglie compatibili con 3,3 V" if ok else f"{b1} {b4}")


def B11():
    bad, _ = _pinchk("Q2", {"1": ("S2", "GND"), "2": ("G2", "LATCH_ON"), "6": ("D2", "LATCH_G"), "4": ("S1", "GND"), "5": ("G1", "RST_G"), "3": ("D1", "NRESET")})
    return ("PASS" if not bad else "FAIL"), ("FET {1 S,2 G,6 D}: GND/LATCH_ON/LATCH_G; FET {4 S,5 G,3 D}: GND/RST_G/NRESET; etichette 1/2 del simbolo LCSC scambiate ma FET identici" if not bad else f"{bad}")


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

def B15():
    bad, _ = _pinchk("U7", {"1": ("SCL/SPC", "I2C_SCL"), "2": ("CS", "3V3"), "3": ("SDO/SA0", "GND"), "4": ("SDA/SDI/SDO", "I2C_SDA"), "5": ("RES", "GND"),
                            "6": ("GND", "GND"), "7": ("GND", "GND"), "8": ("GND", "GND"), "9": ("VDD", "3V3"), "10": ("VDD_IO", "3V3")})
    return ("PASS" if not bad else "FAIL"), ("U7 LIS2DH12: SCL/SDA su I2C, CS a 3V3 (modo I2C), SA0 a GND (0x18, diverso dal VM3011 0x61), RES e 6-8 a GND, "
                                             "VDD e VDD_IO 3V3, INT1/INT2 liberi (campionamento a 10 s); C15 100 nF + C5 4,7 uF vicini" if not bad else f"{bad}")
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def D16():
    d = D(); e = d.C["U1"][1]
    pin = {n: k for k, n in e.items()}
    ok = (pin.get("MIC_WAKE") == "3" and pin.get("I2C_SDA") == "22" and pin.get("I2C_SCL") == "4" and pin.get("BUZ_G") == "6"
          and not any(f.startswith("R") and n in ("I2C_SDA", "I2C_SCL") for r, (f, p, _) in d.C.items() for n in p.values())
          and d.C["BZP"][1]["1"] == "VSYS" and d.C["BZN"][1]["1"] == "BUZ_N")
    return ("PASS" if ok else "FAIL"), ("MIC_WAKE su P0.03 (pad 3), I2C su P0.07/P0.28 con pull-up interni del nRF (~13 k, 100 kHz, piste corte), "
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STATO = {"A01": "rieseguo l'ERC con kicad-cli", "A02": "rieseguo il DRC con parità schema e scollegati", "A03": "DRC severo su una copia con le regole ignorate riattivate",
         "A04": "estraggo regole, via e distanze dei fori con pcbnew", "A05": "conto le isole del piano GND In1", "A06": "estraggo il zip, riesporto i Gerber e confronto il contorno con il DXF",
         "A07": "cerco via dentro i pad SMD con le forme reali", "A08": "confronto riga per riga Gerber del zip ed export fresco", "A09": "riesporto la netlist e leggo gli avvisi",
         "B07": "confronto pin MCP73832 con simbolo e reti, R PROG e pagina JLC C38066", "B08": "verifico che STAT sia open-drain e senza pull-up verso il 5V",
         "C01": "rieseguo il confronto simbolo-impronta-def-netlist-pcb", "E01": "riesporto il pos e confronto riferimenti BOM/CPL", "E02": "codici LCSC, Value e conteggio Extended con C38066",
         "E03": "rileggo la pagina JLC dell'E73", "G01": "strati presenti nel nuovo zip", "H05": "riga STAT di pinout.md contro il caricatore montato"}

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
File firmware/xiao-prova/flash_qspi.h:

// notªpad - driver minimo della flash QSPI della XIAO nRF52840 Sense (Puya P25Q16H, 2 MB) sopra nrfx_qspi.
// Perche' non Adafruit_SPIFlash: la libreria utente omonima (versione piu' recente) rompe la compilazione di Bluefruit.
// Stessa sequenza della libreria (QE, lettura 0x6B quad, scrittura 0x32 quad, WREN esplicito, attesa del bit WIP).
// Tutti gli accessi sono a indirizzi multipli di 4; la scrittura e' una pagina da 256 byte alla volta.
#pragma once
#include <Arduino.h>
#include "nrfx_qspi.h"

class FlashQspi {
 public:
  bool begin() {
    if (attiva) return true;
    nrfx_qspi_config_t cfg = {};
    cfg.xip_offset = 0;
    cfg.pins.sck_pin = (uint8_t)g_ADigitalPinMap[PIN_QSPI_SCK];
    cfg.pins.csn_pin = (uint8_t)g_ADigitalPinMap[PIN_QSPI_CS];
    cfg.pins.io0_pin = (uint8_t)g_ADigitalPinMap[PIN_QSPI_IO0];
    cfg.pins.io1_pin = (uint8_t)g_ADigitalPinMap[PIN_QSPI_IO1];
    cfg.pins.io2_pin = (uint8_t)g_ADigitalPinMap[PIN_QSPI_IO2];
    cfg.pins.io3_pin = (uint8_t)g_ADigitalPinMap[PIN_QSPI_IO3];
    cfg.prot_if.readoc = NRF_QSPI_READOC_READ4O;     // 0x6B
    cfg.prot_if.writeoc = NRF_QSPI_WRITEOC_PP4O;     // 0x32
    cfg.prot_if.addrmode = NRF_QSPI_ADDRMODE_24BIT;
    cfg.prot_if.dpmconfig = false;
    cfg.phy_if.sck_delay = 1;
    cfg.phy_if.dpmen = false;
    cfg.phy_if.spi_mode = NRF_QSPI_MODE_0;
    cfg.phy_if.sck_freq = NRF_QSPI_FREQ_32MDIV2;      // 16 MHz (32 MHz non e' affidabile su nRF52840)
    cfg.irq_priority = 7;
    if (nrfx_qspi_init(&cfg, NULL, NULL) != NRFX_SUCCESS) return false;   // senza callback: API bloccante
    attiva = true;
    delay(6);
    uint8_t id[3] = {0, 0, 0};
    if (!leggiCmd(0x9F, id, 3) || id[0] != 0x85 || id[2] != 0x15) { end(); return false; }   // Puya, 2 MB
    uint8_t s2 = 0;
    leggiCmd(0x35, &s2, 1);
    if (!(s2 & 0x02)) {                                 // bit QE (quad enable)
      wren();
      const uint8_t d[2] = {0x00, 0x02};
      scriviCmd(0x01, d, 2);
      attendi(100);
    }
    return true;
  }
  void end() {
    if (!attiva) return;
    attendi(100);
    nrfx_qspi_uninit();
    attiva = false;
  }
  uint32_t size() const { return 2UL * 1024 * 1024; }

  // lunghezza qualsiasi, indirizzo multiplo di 4; ritorna len se ok, 0 se errore
  uint32_t readBuffer(uint32_t addr, uint8_t *buf, uint32_t len) {
    if (!attiva || (addr & 3)) return 0;
    uint32_t resto = len;
    while (resto) {
      uint32_t n = min(resto, (uint32_t)sizeof(tmp));
      uint32_t n4 = (n + 3) & ~3UL;
      if (!attendi(100)) return 0;
      if (nrfx_qspi_read(tmp, n4, addr) != NRFX_SUCCESS) return 0;
      memcpy(buf, tmp, n);
      buf += n; addr += n; resto -= n;
    }
    return len;
  }
  // una pagina (non oltre il confine di 256 byte), indirizzo multiplo di 4
  uint32_t writeBuffer(uint32_t addr, const uint8_t *buf, uint32_t len) {
    if (!attiva || (addr & 3) || len == 0 || len > 256 || (addr & 255) + len > 256) return 0;
    if (!attendi(100)) return 0;
    wren();
    memset(tmp, 0xFF, sizeof(tmp));
    memcpy(tmp, buf, len);
    uint32_t n4 = (len + 3) & ~3UL;
    if (nrfx_qspi_write(tmp, n4, addr) != NRFX_SUCCESS) return 0;
    return len;
  }
  // cancella un settore da 4 KB (comando 0x20), indirizzo multiplo di 4096; tipico 45 ms, massimo ~300 ms
  bool eraseSector(uint32_t addr) {
    if (!attiva || (addr & 4095) || addr >= size() || !attendi(100)) return false;
    wren();
    const uint8_t a[3] = {(uint8_t)(addr >> 16), (uint8_t)(addr >> 8), (uint8_t)addr};
    if (!scriviCmd(0x20, a, 3)) return false;
    return attendi(1000);
  }
  // --- operazioni non bloccanti (notªpad): il loop controlla occupata() prima di ogni accesso ---
  bool occupata() {
    uint8_t st = 0xFF;
    if (!leggiCmd(0x05, &st, 1)) return true;
    return st & 0x01;
  }
  // avvia la cancellazione di un settore da 4 KB e torna subito (finisce quando occupata() torna falso)
  bool eraseAvvia(uint32_t addr) {
    if (!attiva || (addr & 4095) || addr >= size()) return false;
    wren();
    const uint8_t a[3] = {(uint8_t)(addr >> 16), (uint8_t)(addr >> 8), (uint8_t)addr};
    return scriviCmd(0x20, a, 3);
  }
  bool eraseChip() {
    if (!attiva || !attendi(100)) return false;
    wren();
    if (!comando(0xC7, NULL, 0, NULL, 0)) return false;
    return attendi(60000);                              // tipico 5-15 s
  }
  // attende la fine di una scrittura/cancellazione (bit WIP del registro di stato)
  bool attendi(uint32_t timeoutMs) {
    uint32_t t0 = millis();
    while (true) {
      uint8_t st = 0xFF;
      if (!leggiCmd(0x05, &st, 1)) return false;
      if (!(st & 0x01)) return true;
      if (millis() - t0 > timeoutMs) return false;
      if (ciclo) ciclo();                               // 0.6.1: l'attesa lunga (cancellazione chip, fino a 15 s) serve il watchdog
      delay(1);
    }
  }

 void (*ciclo)() = nullptr;      // chiamata a ogni giro delle attese (watchdog)

 private:
  bool attiva = false;
  alignas(4) uint8_t tmp[256];
  bool comando(uint8_t op, const uint8_t *tx, uint8_t nTx, uint8_t *rx, uint8_t nRx) {
    nrf_qspi_cinstr_conf_t c = {};
    c.opcode = op;
    c.length = (nrf_qspi_cinstr_len_t)((nTx > nRx ? nTx : nRx) + 1);
    c.io2_level = true;
    c.io3_level = true;
    c.wipwait = false;
    c.wren = false;
    return nrfx_qspi_cinstr_xfer(&c, tx, rx) == NRFX_SUCCESS;
  }
  bool leggiCmd(uint8_t op, uint8_t *rx, uint8_t n) { return comando(op, NULL, 0, rx, n); }
  bool scriviCmd(uint8_t op, const uint8_t *tx, uint8_t n) { return comando(op, tx, n, NULL, 0); }
  void wren() { comando(0x06, NULL, 0, NULL, 0); }
};

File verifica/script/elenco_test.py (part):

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  "Confronto a vista una tantum con la tabella 'Pin definition' del manuale Ebyte (il simbolo LCSC e l'impronta hanno la stessa origine)", "test_C_simbolo_impronta.py")
T("B02", "E73: nessun pin non esposto; pin 'low frequency'", "Pin usati contro i 43 pad del modulo e contro la lista nRF52840 'Standard drive, low frequency I/O only'", ["E73_EASYEDA", "NRF_PIN", "DEF"],
  "Nessuno di P0.11/14/16/19/21/23/25/27, P1.01; segnali veloci (QSPI, PDM) non su pin low-frequency",
  "Nessun pin non esposto usato. Su pin low-frequency (<= 10 kHz) solo segnali lenti: TOUCH_B P0.31, HOLD P0.29, VBAT P0.02, MOTOR_G P0.30, VBUS P0.28, LED3 G/B P1.02/P1.04. QSPI e PDM su pin normali (P1.09 non è nella lista)",
  "PASS", "media", "Firmware: PWM dei LED su P1.02/P1.04 e del motore su P0.30 <= 10 kHz, drive standard", "")
T("B03", "E73: alimentazione (VDD, VDDH, DCCH, VBUS, GND)", "Reti dei pad 19/23/25/27/5/21/24", ["DEF", "NET", "E73_EASYEDA"],
  "Modalità normale: VDD e VDDH entrambi a 3V3, DCCH libero, VBUS libero se non si usa USB, tutte le GND collegate",
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  "Accettabile; eventualmente R7 a 47k nei lotti futuri", "")
T("D07", "LDO XC6206: dropout, picco, condensatori", "Calcolo con dropout tipico e carichi di picco", ["DEF", "JLC_LDO", "PCB"],
  "3,3 V stabili fino a 3,5 V di batteria; Cin/Cout >= 1 uF", "Picco ~55 mA (radio 17 mA + NAND ~25-35 mA + mic ~1,5 mA + CPU): dropout ~60-140 mV, regola fino a ~3,4-3,45 V. Cout 1 uF + 4,7 uF vicini; Cin C3 1 uF su VSYS a ~7 mm dal pin di ingresso", "WARN", "bassa",
  "Nessuna per l'ordine; al collaudo verificare l'assenza di oscillazioni sul 3V3", "")
T("D08", "LED: correnti reali", "(VSYS - Vf - VOL)/470 con Vf JLC", ["JLC_LED", "DEF"], "colori visibili su tutta la scarica, corrente entro il GPIO",
  "Rosso: 2,8 mA a 3,5 V, 4,3 mA a 4,2 V (serve high-drive H0 per il pieno). Verde/blu (Vf 2,5-3,5 V, tip. ~3,0): ~0,8 mA a 3,5 V, ~2,3 mA a 4,2 V; con Vf al massimo a 3,5 V restano spenti. Catodo da spento a ~2,0-2,8 V < VDD: nessuna iniezione", "WARN", "bassa",
  "Firmware: drive H0S1 sui catodi; aspettarsi verde/blu fiochi sotto ~3,6 V", "")
T("D09", "Motorino: MOSFET, diodo, pull-down", "Reti di Q4, D4, R10, M1P/M1N", ["DEF", "NET"], "MOS a basso lato, diodo di ricircolo, gate a massa da spento",
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
# ---------------- E ----------------
T("D16", "Standby acustico, I2C e cicalino", "Reti e datasheet VM3011 contro i pin del nRF", ["DS_VM3011", "DEF", "PINOUT"],
  "DOUT su un GPIO, I2C con indirizzi distinti, cicalino da VSYS con FET e diodo", "", "IN_ATTESA", "media", "", "giro2.py")
T("E01", "Riferimenti in BOM e CPL", "Insieme dei ref di def.py (esclusi i montati a mano) contro BOM, CPL, jlc/BOM", ["DEF", "BOM", "CPL"],
  "43 componenti SMD in entrambi, nessun extra", "43 in CPL e in BOM (19 righe), jlc/ BOM uguale; J1-J4, BT1P/N, M1P/N, TPA/TPB esclusi", "PASS", "alta", "", "test_E_bom_cpl.py")
T("E02", "Codici LCSC, package, Basic/Extended", "Pagine JLC dei codici", ["JLC_E73", "JLC_NAND", "JLC_MIC", "JLC_CHG", "JLC_TTP", "JLC_LED", "JLC_Q2", "JLC_LDO", "JLC_Q1", "JLC_Q4", "JLC_D", "JLC_C5", "BOM"],
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

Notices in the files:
README.md:
License:
- **Hardware** (KiCad project, Gerber and fabrication files, enclosure, renders): [CERN-OHL-S-2.0](LICENSE-HARDWARE), strongly reciprocal: modified hardware must stay open.
- **Software** (scripts, firmware, app, MCP server) and documentation: [MIT](LICENSE).
- Third-party symbols and footprints in `kicad/lib/` (generated from LCSC/EasyEDA with easyeda2kicad) keep their original terms.
Hardware: CERN-OHL-S-2.0
